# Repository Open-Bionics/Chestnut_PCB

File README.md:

# Chestnut_PCB
Electronics &amp; software files for the Chestnut/Chestnut+ PCB for the Brunel hand

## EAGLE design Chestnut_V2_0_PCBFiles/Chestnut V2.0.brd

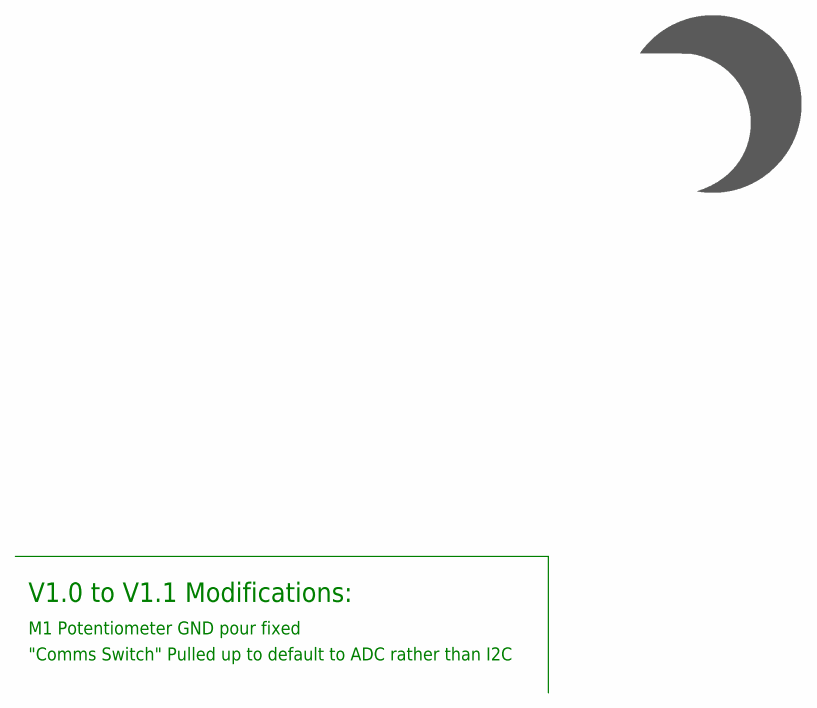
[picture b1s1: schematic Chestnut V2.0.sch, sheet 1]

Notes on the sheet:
V1.0 to V1.1 Modifications:
M1 Potentiometer GND pour fixed
"Comms Switch" Pulled up to default to ADC rather than I2C

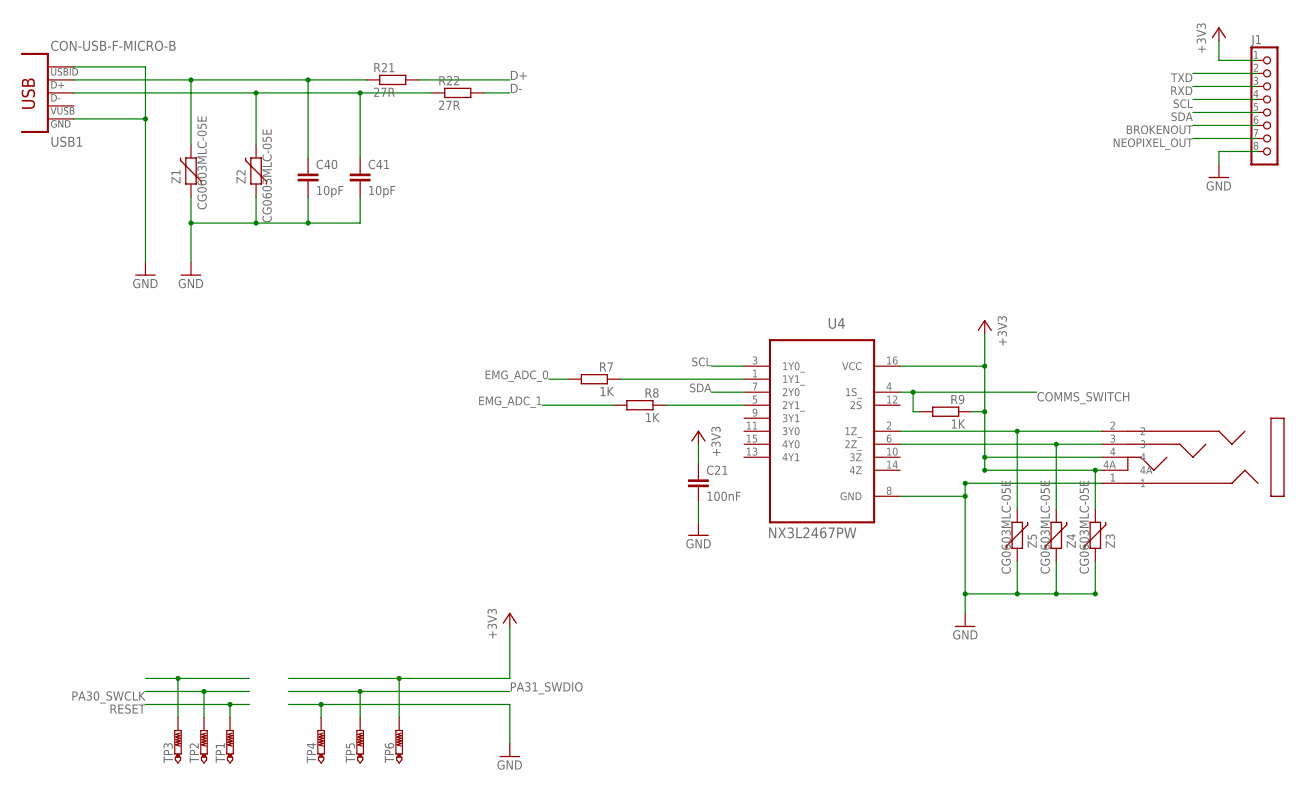
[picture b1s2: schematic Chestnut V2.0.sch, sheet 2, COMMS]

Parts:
C21: 100nF; C0402
C40, C41: 10pF; C0402
J1: CON_HEADER_1X08-PTH; M1X8
R7, R8, R9: 1K; R0402
R21, R22: 27R; R0402
TP1, TP2, TP3, TP4, TP5, TP6: PTR1TP11R; TP11R
U4: NX3L2467PW; SOP65P640X110-16N
U$7: LUMBERG_1503-13-VP3
USB1: CON-USB-F-MICRO-B; CONN_USB_MICRO-B
Z1, Z2, Z3, Z4, Z5: CG0603MLC-05E; CT/CN0603

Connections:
+3V3: C21.1, J1.1, R9.1, TP6.TP, U4.16 (VCC), U$7.4, U$7.4A, Z3.2; also elsewhere on the board
BROKENOUT: J1.6; also elsewhere on the board
COMMS_SWITCH: R9.2, U4.4 (1S_); also elsewhere on the board
D+: R21.2; also elsewhere on the board
D-: R22.2; also elsewhere on the board
EMG_ADC_0: R7.2; also elsewhere on the board
EMG_ADC_1: R8.2; also elsewhere on the board
GND: C21.2, C40.2, C41.2, J1.8, TP4.TP, U4.8 (GND), U$7.1, USB1.P4 (USBID), USB1.P5 (GND), Z1.1, Z2.1, Z3.1, Z4.1, Z5.1; also elsewhere on the board
unnamed: U4.6 (2Z_), U$7.3, Z4.2
unnamed: C41.1, R22.1, USB1.P2 (D-), Z2.2
unnamed: C40.1, R21.1, USB1.P3 (D+), Z1.2
unnamed: U4.2 (1Z_), U$7.2, Z5.2
unnamed: R7.1, U4.1 (1Y1_)
unnamed: R8.1, U4.5 (2Y1_)
NEOPIXEL_OUT: J1.7; also elsewhere on the board
PA30_SWCLK: TP2.TP; also elsewhere on the board
PA31_SWDIO: TP5.TP; also elsewhere on the board
RESET: TP1.TP; also elsewhere on the board
RXD: J1.3; also elsewhere on the board
SCL: J1.4, U4.3 (1Y0_); also elsewhere on the board
SDA: J1.5, U4.7 (2Y0); also elsewhere on the board
TXD: J1.2; also elsewhere on the board

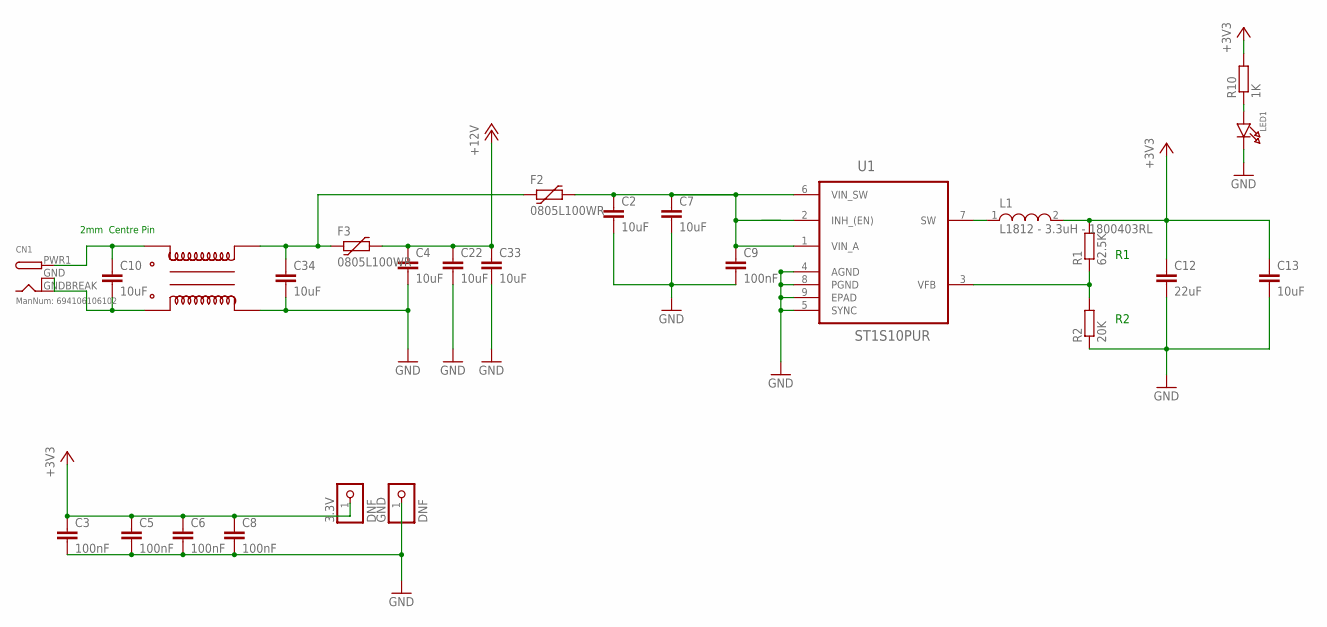
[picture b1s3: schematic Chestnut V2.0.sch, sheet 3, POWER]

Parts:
3.3V: DNF; 1X01_ROUND
C2, C4, C7, C10, C13, C22, C33, C34: 10uF; C0805
C3, C5, C6, C8, C9: 100nF; C0402
C12: 22uF; C1210
CN1: ManNum: 694106106102; DCJACK_2MM_SMT
F2, F3: 0805L100WR; PTC0805
GND: DNF; 1X01_ROUND
L1: L1812 - 3.3uH - 1800403RL; L1812
LED1: LED0603; CHIPLED_0603
R1: 62.5K; R0603
R2: 20K; R0603
R10: 1K; R0402
U1: ST1S10PUR; DFN400X400X100-9N
U$5: DLW5BTN501SQ2L

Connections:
12VFUSED: C2.1, C7.1, C9.1, F2.2, U1.1 (VIN_A), U1.2 (INH_(EN)), U1.6 (VIN_SW)
+3V3: 3.3V.1, C3.1, C5.1, C6.1, C8.1, C12.1, C13.1, L1.2, R1.2, R10.2; also elsewhere on the board
+12V: C4.1, C22.1, C33.1, F3.2; also elsewhere on the board
GND: C2.2, C3.2, C4.2, C5.2, C6.2, C7.2, C8.2, C9.2, C12.2, C13.2, C22.2, C33.2, C34.2, GND.1, LED1.C, R2.1, U1.4 (AGND), U1.5 (SYNC), U1.8 (PGND), U1.9 (EPAD), U$5.4; also elsewhere on the board
unnamed: LED1.A, R10.1
unnamed: L1.1, U1.7 (SW)
unnamed: C34.1, F2.1, F3.1, U$5.2
unnamed: R1.1, R2.2, U1.3 (VFB)
unnamed: C10.2, CN1.GND (GNDBREAK), CN1.GNDBREAK (GND), U$5.3
unnamed: C10.1, CN1.PWR1 (PWR), U$5.1

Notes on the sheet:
2mm Centre Pin

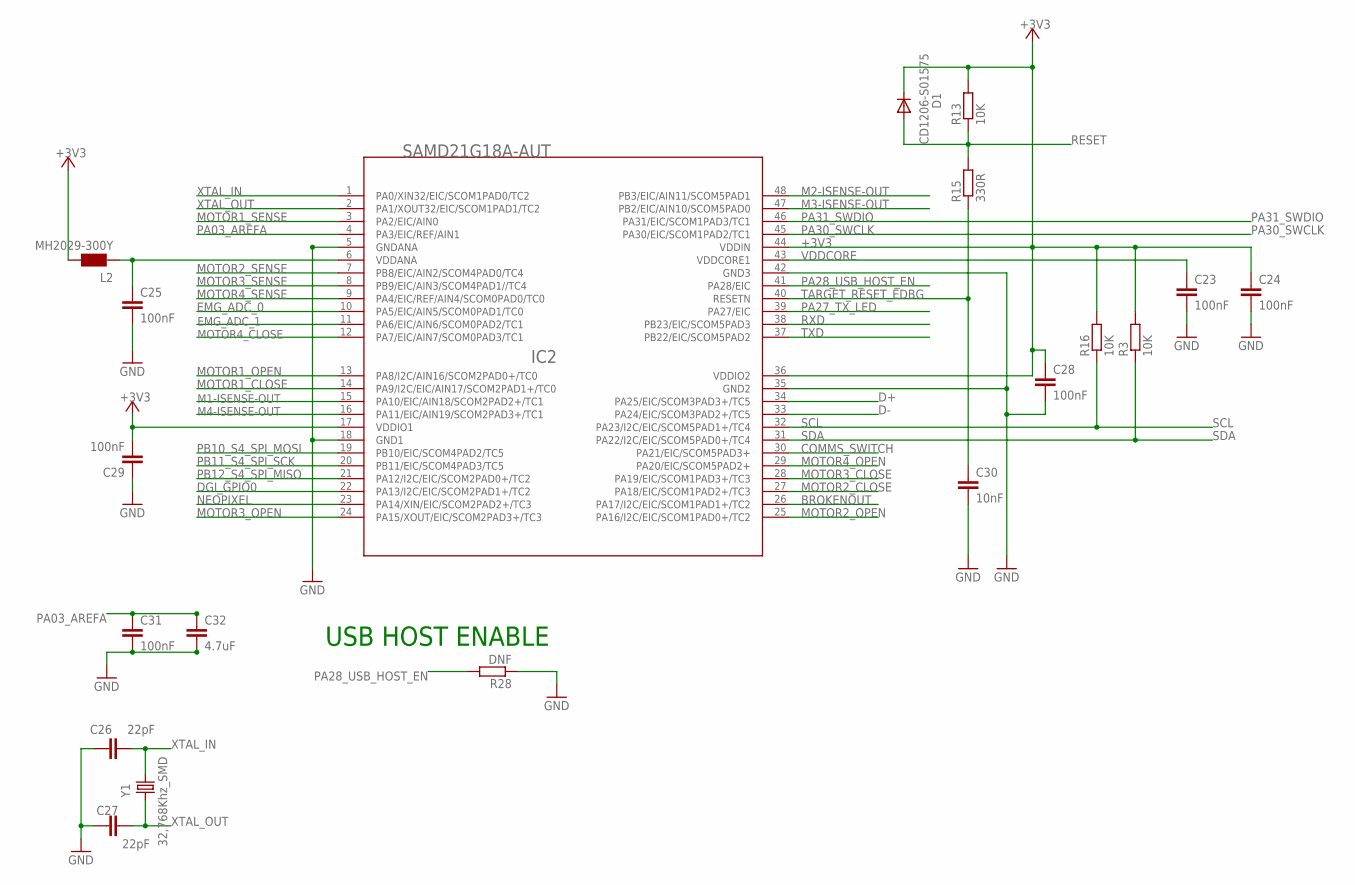
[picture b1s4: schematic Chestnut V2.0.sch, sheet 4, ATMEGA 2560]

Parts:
C23, C24, C25, C28, C29, C31: 100nF; C0402
C26, C27: 22pF; C0402
C30: 10nF; C0402
C32: 4.7uF; C0603
D1: CD1206-S01575; MINIMELF
IC2: SAMD21G18A-AUT; INTEGRATEDCIRCUITS_TQFP48-7X7
L2: MH2029-300Y; 0805
R3, R13, R16: 10K; R0402
R15: 330R; R0402
R28: DNF; R0402
Y1: 32,768Khz_SMD; RESONATOR_EPSON_FC_145

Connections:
+3V3: C24.1, C28.1, C29.2, D1.C, IC2.17 (VDDIO1), IC2.36 (VDDIO2), IC2.44 (VDDIN), L2.2, R3.2, R13.2, R16.2; also elsewhere on the board
BROKENOUT: IC2.26 (PA17/I2C/EIC/SCOM1PAD1+/TC2); also elsewhere on the board
COMMS_SWITCH: IC2.30 (PA21/EIC/SCOM5PAD3+); also elsewhere on the board
D+: IC2.34 (PA25/EIC/SCOM3PAD3+/TC5); also elsewhere on the board
D-: IC2.33 (PA24/EIC/SCOM3PAD2+/TC5); also elsewhere on the board
DGI_GPIO0: IC2.22 (PA13/I2C/EIC/SCOM2PAD1+/TC2)
EMG_ADC_0: IC2.10 (PA5/EIC/AIN5/SCOM0PAD1/TC0); also elsewhere on the board
EMG_ADC_1: IC2.11 (PA6/EIC/AIN6/SCOM0PAD2/TC1); also elsewhere on the board
GND: C23.2, C24.2, C25.2, C26.1, C27.1, C28.2, C29.1, C30.2, C31.2, C32.2, IC2.5 (GNDANA), IC2.18 (GND1), IC2.35 (GND2), IC2.42 (GND3), R28.1; also elsewhere on the board
M1-ISENSE-OUT: IC2.15 (PA10/EIC/AIN18/SCOM2PAD2+/TC1); also elsewhere on the board
M2-ISENSE-OUT: IC2.48 (PB3/EIC/AIN11/SCOM5PAD1); also elsewhere on the board
M3-ISENSE-OUT: IC2.47 (PB2/EIC/AIN10/SCOM5PAD0); also elsewhere on the board
M4-ISENSE-OUT: IC2.16 (PA11/EIC/AIN19/SCOM2PAD3+/TC1); also elsewhere on the board
MOTOR1_CLOSE: IC2.14 (PA9/I2C/EIC/AIN17/SCOM2PAD1+/TC0); also elsewhere on the board
MOTOR1_OPEN: IC2.13 (PA8/I2C/AIN16/SCOM2PAD0+/TC0); also elsewhere on the board
MOTOR1_SENSE: IC2.3 (PA2/EIC/AIN0); also elsewhere on the board
MOTOR2_CLOSE: IC2.27 (PA18/EIC/SCOM1PAD2+/TC3); also elsewhere on the board
MOTOR2_OPEN: IC2.25 (PA16/I2C/EIC/SCOM1PAD0+/TC2); also elsewhere on the board
MOTOR2_SENSE: IC2.7 (PB8/EIC/AIN2/SCOM4PAD0/TC4); also elsewhere on the board
MOTOR3_CLOSE: IC2.28 (PA19/EIC/SCOM1PAD3+/TC3); also elsewhere on the board
MOTOR3_OPEN: IC2.24 (PA15/XOUT/EIC/SCOM2PAD3+/TC3); also elsewhere on the board
MOTOR3_SENSE: IC2.8 (PB9/EIC/AIN3/SCOM4PAD1//TC4); also elsewhere on the board
MOTOR4_CLOSE: IC2.12 (PA7/EIC/AIN7/SCOM0PAD3/TC1); also elsewhere on the board
MOTOR4_OPEN: IC2.29 (PA20/EIC/SCOM5PAD2+); also elsewhere on the board
MOTOR4_SENSE: IC2.9 (PA4/EIC/REF/AIN4/SCOM0PAD0/TC0); also elsewhere on the board
unnamed: C25.1, IC2.6 (VDDANA), L2.1
NEOPIXEL: IC2.23 (PA14/XIN/EIC/SCOM2PAD2+/TC3); also elsewhere on the board
PA03_AREFA: C31.1, C32.1, IC2.4 (PA3/EIC/REF/AIN1)
PA27_TX_LED: IC2.39 (PA27/EIC)
PA28_USB_HOST_EN: IC2.41 (PA28/EIC), R28.2
PA30_SWCLK: IC2.45 (PA30/EIC/SCOM1PAD2/TC1); also elsewhere on the board
PA31_SWDIO: IC2.46 (PA31/EIC/SCOM1PAD3/TC1); also elsewhere on the board
PB10_S4_SPI_MOSI: IC2.19 (PB10/EIC/SCOM4PAD2/TC5)
PB11_S4_SPI_SCK: IC2.20 (PB11/EIC/SCOM4PAD3/TC5)
PB12_S4_SPI_MISO: IC2.21 (PA12/I2C/EIC/SCOM2PAD0+/TC2)
RESET: D1.A, R13.1, R15.2; also elsewhere on the board
RXD: IC2.38 (PB23/EIC/SCOM5PAD3); also elsewhere on the board
SCL: IC2.32 (PA23/I2C/EIC/SCOM5PAD1+/TC4), R16.1; also elsewhere on the board
SDA: IC2.31 (PA22/I2C/EIC/SCOM5PAD0+/TC4), R3.1; also elsewhere on the board
TARGET_RESET_EDBG: C30.1, IC2.40 (RESETN), R15.1
TXD: IC2.37 (PB22/EIC/SCOM5PAD2); also elsewhere on the board
VDDCORE: C23.1, IC2.43 (VDDCORE1)
XTAL_IN: C26.2, IC2.1 (PA0/XIN32/EIC/SCOM1PAD0/TC2), Y1.P$2 (2)
XTAL_OUT: C27.2, IC2.2 (PA1/XOUT32/EIC/SCOM1PAD1/TC2), Y1.P$1 (1)

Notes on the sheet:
USB HOST ENABLE

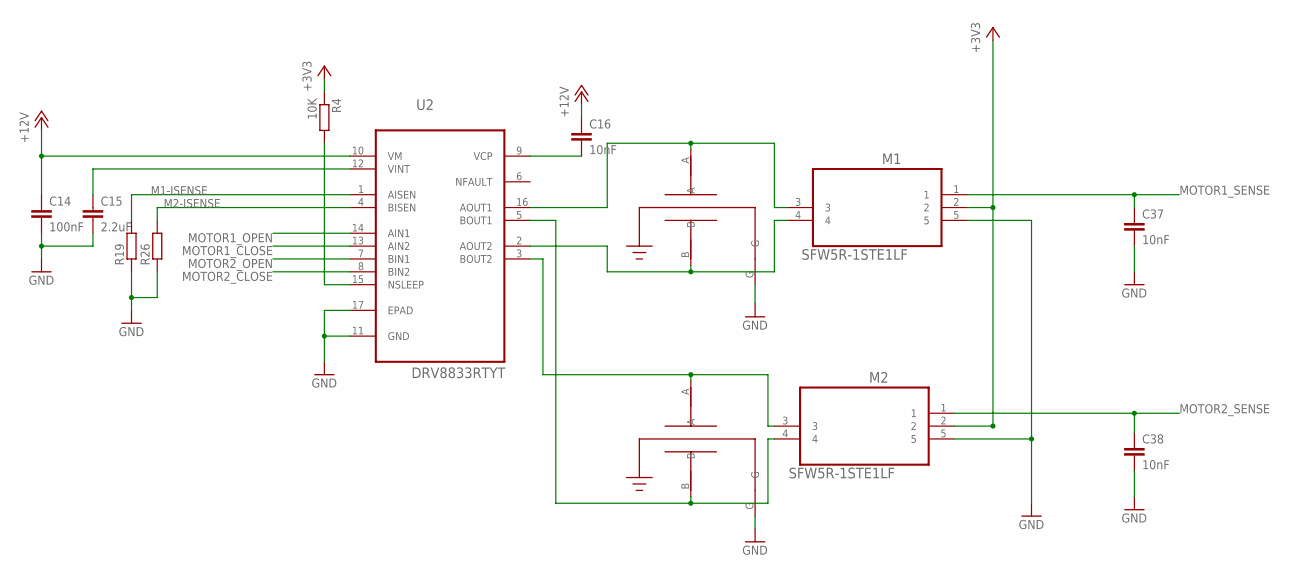
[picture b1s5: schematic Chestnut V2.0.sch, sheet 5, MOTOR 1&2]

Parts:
C14: 100nF; C0402
C15: 2.2uF; C0603
C16, C37, C38: 10nF; C0402
M1, M2: SFW5R-1STE1LF; FCI_SFW5R-1STE1LF
R4: 10K; R0402
R19, R26: R-EU_R0805; R0805
U2: DRV8833RTYT; QFN65P400X400X80-17N
U$8, U$19: 101X14N330MV4T_X2Y_0603

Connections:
+3V3: M1.2, M2.2, R4.1; also elsewhere on the board
+12V: C14.1, C16.1, U2.10 (VM); also elsewhere on the board
GND: C14.2, C15.2, C37.2, C38.2, M1.5, M2.5, R19.1, R26.1, U2.11 (GND), U2.17 (EPAD), U$8.G, U$19.G; also elsewhere on the board
M1-ISENSE: R19.2, U2.1 (AISEN); also elsewhere on the board
M2-ISENSE: R26.2, U2.4 (BISEN); also elsewhere on the board
MOTOR1_CLOSE: U2.13 (AIN2); also elsewhere on the board
MOTOR1_OPEN: U2.14 (AIN1); also elsewhere on the board
MOTOR1_SENSE: C37.1, M1.1; also elsewhere on the board
MOTOR2_CLOSE: U2.8 (BIN2); also elsewhere on the board
MOTOR2_OPEN: U2.7 (BIN1); also elsewhere on the board
MOTOR2_SENSE: C38.1, M2.1; also elsewhere on the board
unnamed: C16.2, U2.9 (VCP)
unnamed: M1.3, U2.16 (AOUT1), U$19.A
unnamed: M1.4, U2.2 (AOUT2), U$19.B
unnamed: M2.4, U2.5 (BOUT1), U$8.B
unnamed: M2.3, U2.3 (BOUT2), U$8.A
unnamed: R4.2, U2.15 (NSLEEP)
unnamed: C15.1, U2.12 (VINT)

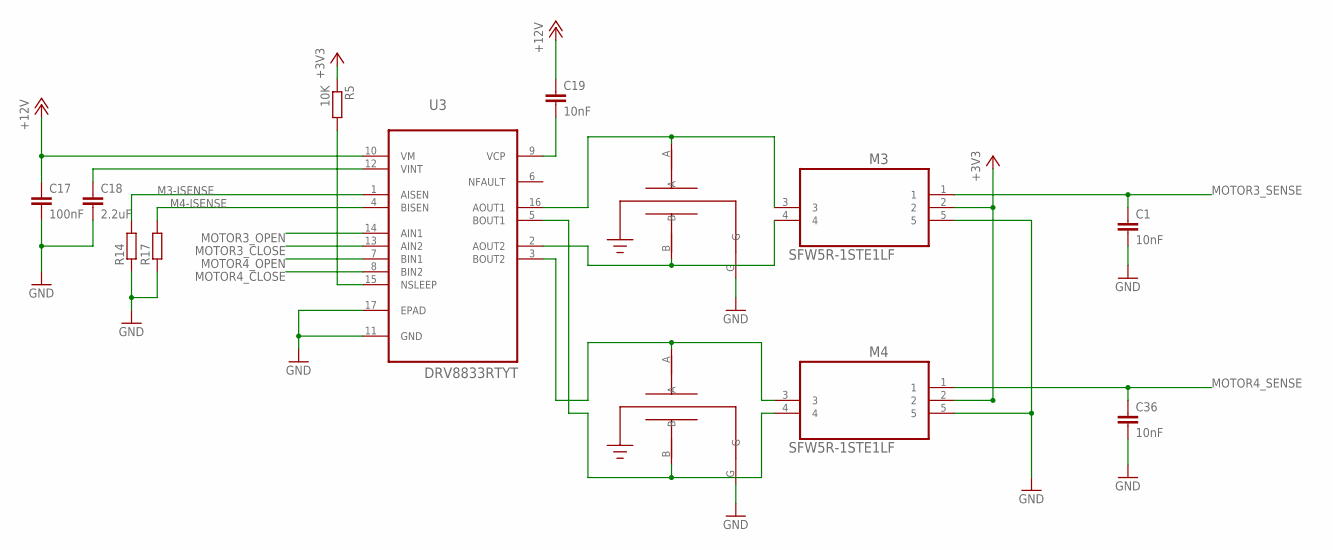
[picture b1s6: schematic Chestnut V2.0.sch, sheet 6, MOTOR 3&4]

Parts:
C1, C19, C36: 10nF; C0402
C17: 100nF; C0402
C18: 2.2uF; C0603
M3, M4: SFW5R-1STE1LF; FCI_SFW5R-1STE1LF
R5: 10K; R0402
R14, R17: R-EU_R0805; R0805
U3: DRV8833RTYT; QFN65P400X400X80-17N
U$9, U$10: 101X14N330MV4T_X2Y_0603

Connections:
+3V3: M3.2, M4.2, R5.1; also elsewhere on the board
+12V: C17.1, C19.1, U3.10 (VM); also elsewhere on the board
GND: C1.2, C17.2, C18.2, C36.2, M3.5, M4.5, R14.1, R17.1, U3.11 (GND), U3.17 (EPAD), U$9.G, U$10.G; also elsewhere on the board
M3-ISENSE: R14.2, U3.1 (AISEN); also elsewhere on the board
M4-ISENSE: R17.2, U3.4 (BISEN); also elsewhere on the board
MOTOR3_CLOSE: U3.13 (AIN2); also elsewhere on the board
MOTOR3_OPEN: U3.14 (AIN1); also elsewhere on the board
MOTOR3_SENSE: C1.1, M3.1; also elsewhere on the board
MOTOR4_CLOSE: U3.8 (BIN2); also elsewhere on the board
MOTOR4_OPEN: U3.7 (BIN1); also elsewhere on the board
MOTOR4_SENSE: C36.1, M4.1; also elsewhere on the board
unnamed: M3.3, U3.16 (AOUT1), U$9.A
unnamed: M3.4, U3.2 (AOUT2), U$9.B
unnamed: M4.4, U3.5 (BOUT1), U$10.B
unnamed: M4.3, U3.3 (BOUT2), U$10.A
unnamed: C19.2, U3.9 (VCP)
unnamed: C18.1, U3.12 (VINT)
unnamed: R5.2, U3.15 (NSLEEP)

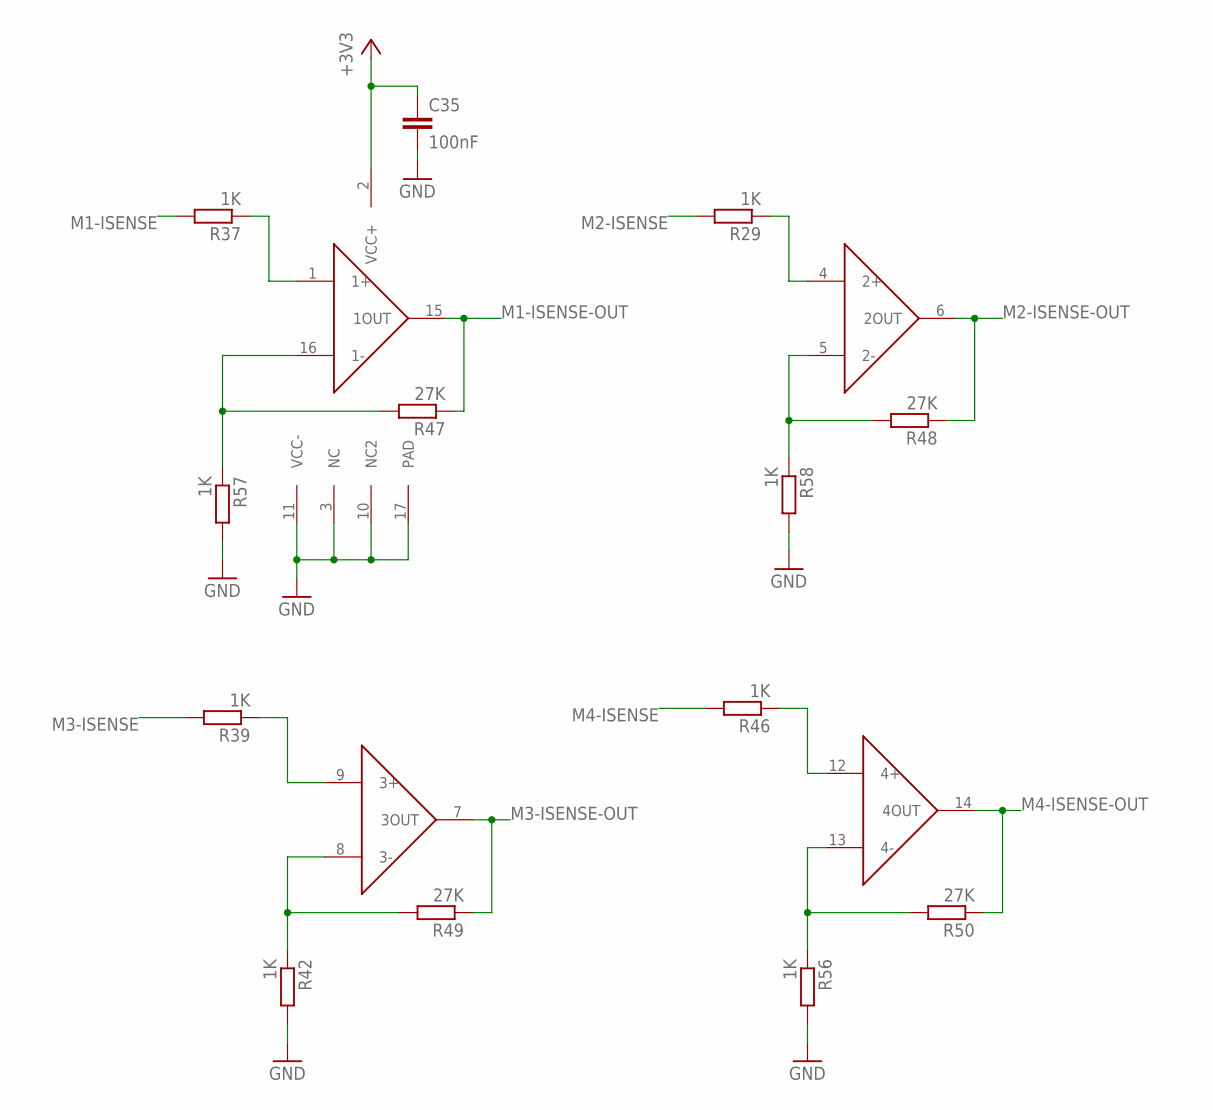
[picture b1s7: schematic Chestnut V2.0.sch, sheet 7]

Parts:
C35: 100nF; C0402
R29, R37, R39, R42, R46, R56, R57, R58: 1K; R0402
R47, R48, R49, R50: 27K; R0402
U$15: TSZ124IQ4T

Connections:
+3V3: C35.1, U$15.2 (VCC+); also elsewhere on the board
GND: C35.2, R42.2, R56.2, R57.2, R58.2, U$15.3 (NC), U$15.10 (NC2), U$15.11 (VCC-), U$15.17 (PAD); also elsewhere on the board
M1-ISENSE: R37.2; also elsewhere on the board
M1-ISENSE-OUT: R47.1, U$15.15 (1OUT); also elsewhere on the board
M2-ISENSE: R29.2; also elsewhere on the board
M2-ISENSE-OUT: R48.1, U$15.6 (2OUT); also elsewhere on the board
M3-ISENSE: R39.2; also elsewhere on the board
M3-ISENSE-OUT: R49.1, U$15.7 (3OUT); also elsewhere on the board
M4-ISENSE: R46.2; also elsewhere on the board
M4-ISENSE-OUT: R50.1, U$15.14 (4OUT); also elsewhere on the board
unnamed: R37.1, U$15.1 (1+)
unnamed: R29.1, U$15.4 (2+)
unnamed: R39.1, U$15.9 (3+)
unnamed: R47.2, R57.1, U$15.16 (1-)
unnamed: R46.1, U$15.12 (4+)
unnamed: R48.2, R58.1, U$15.5 (2-)
unnamed: R42.1, R49.2, U$15.8 (3-)
unnamed: R50.2, R56.1, U$15.13 (4-)

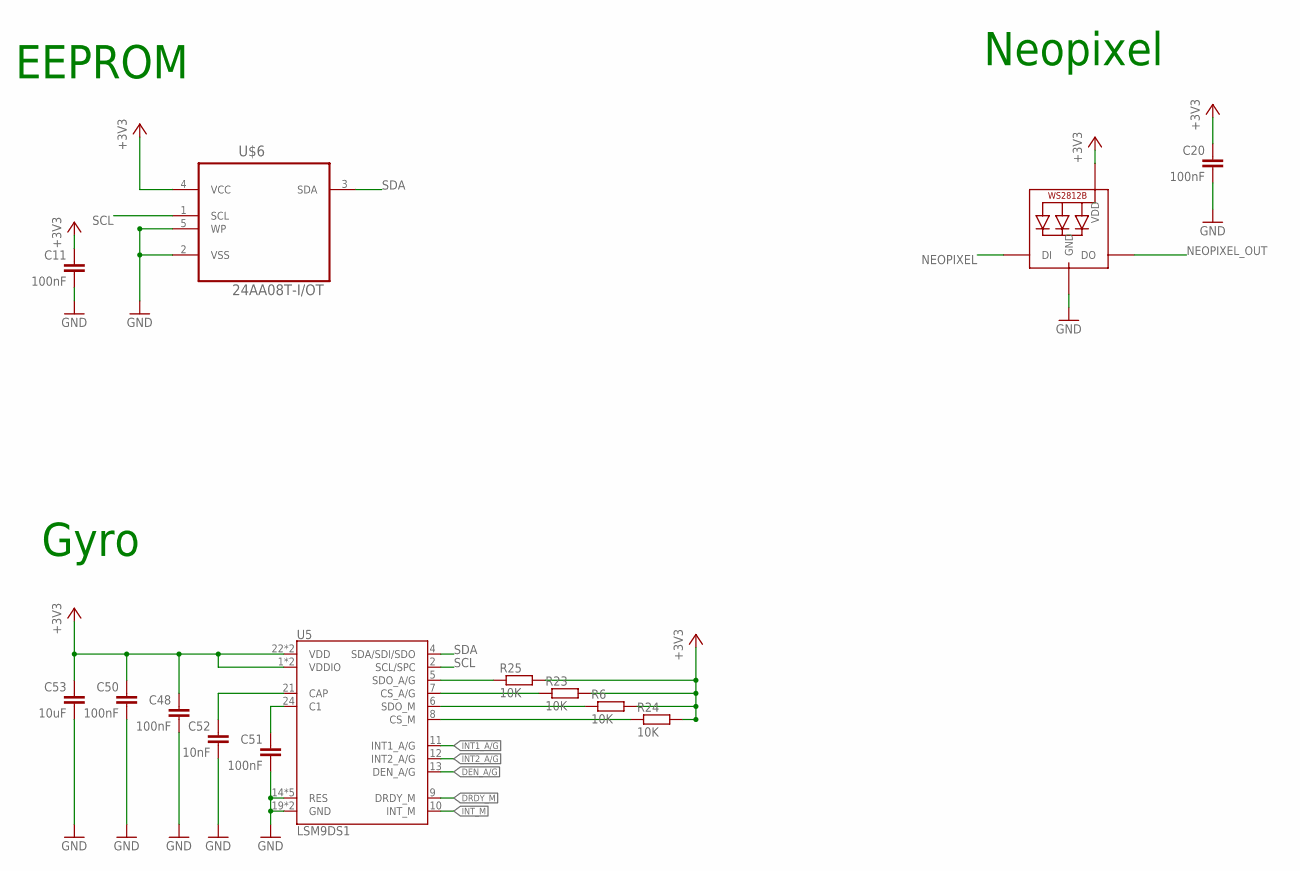
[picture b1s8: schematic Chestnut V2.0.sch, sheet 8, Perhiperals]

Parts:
C11, C20, C48, C50, C51: 100nF; C0402
C52: 10nF; C0402
C53: 10uF; C0805
LED2: WS2812B3535; LED3535
R6, R23, R24, R25: 10K; R0402
U5: LSM9DS1; LGA24-8X4
U$6: 24AA08T-I/OT; SOT95P290X145-5N

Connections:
+3V3: C11.1, C20.1, C48.1, C50.1, C53.1, LED2.2 (VDD), R6.2, R23.2, R24.2, R25.2, U5.1 (VDDIO), U5.3 (VDDIO), U5.22 (VDD), U5.23 (VDD), U$6.4 (VCC); also elsewhere on the board
C1: C51.1, U5.24 (C1)
CAP: C52.1, U5.21 (CAP)
DEN_A/G: U5.13 (DEN_A/G)
DRDY_M: U5.9 (DRDY_M)
GND: C11.2, C20.2, C48.2, C50.2, C51.2, C52.2, C53.2, LED2.4 (GND), U5.14 (RES), U5.15 (RES), U5.16 (RES), U5.17 (RES), U5.18 (RES), U5.19 (GND), U5.20 (GND), U$6.2 (VSS), U$6.5 (WP); also elsewhere on the board
INT1_A/G: U5.11 (INT1_A/G)
INT2_A/G: U5.12 (INT2_A/G)
INT_M: U5.10 (INT_M)
unnamed: R25.1, U5.5 (SDO_A/G)
unnamed: R23.1, U5.7 (CS_A/G)
unnamed: R6.1, U5.6 (SDO_M)
unnamed: R24.1, U5.8 (CS_M)
NEOPIXEL: LED2.1 (DI); also elsewhere on the board
NEOPIXEL_OUT: LED2.3 (DO); also elsewhere on the board
SCL: U5.2 (SCL/SPC), U$6.1 (SCL); also elsewhere on the board
SDA: U5.4 (SDA/SDI/SDO), U$6.3 (SDA); also elsewhere on the board

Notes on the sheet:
EEPROM
Gyro
Neopixel

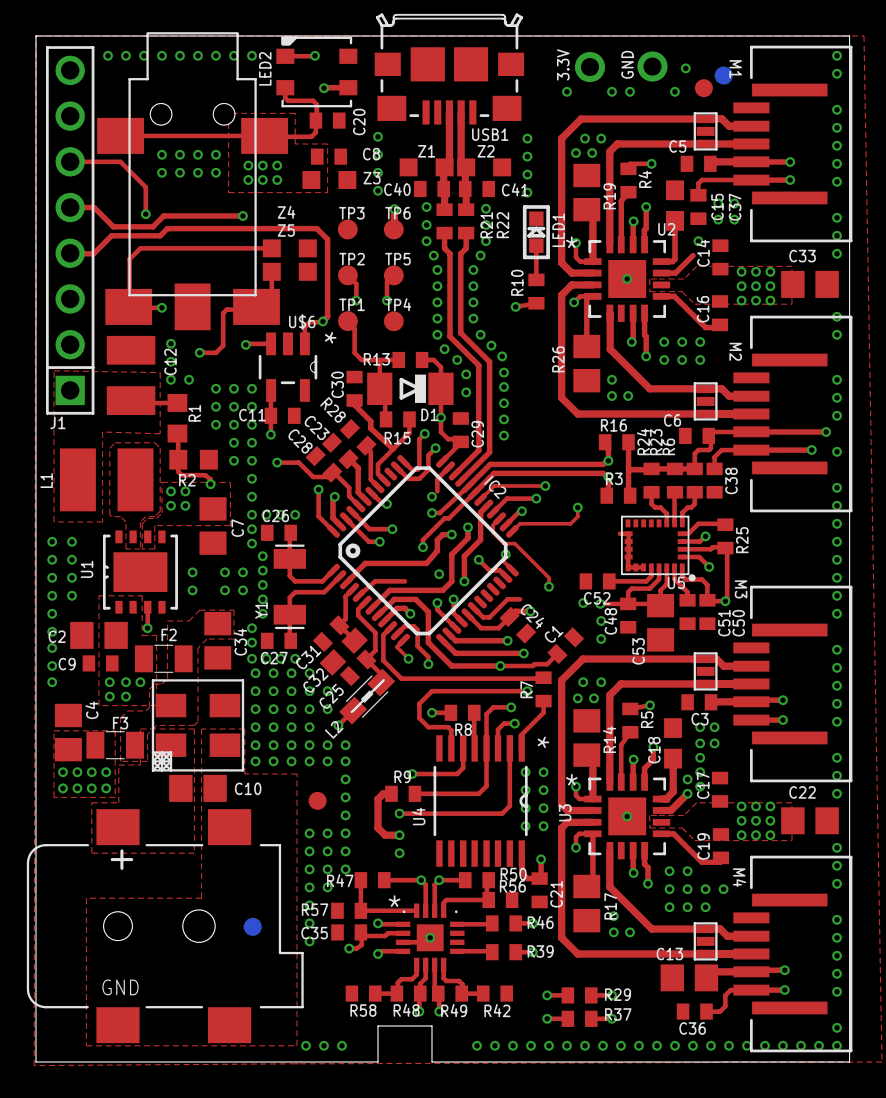
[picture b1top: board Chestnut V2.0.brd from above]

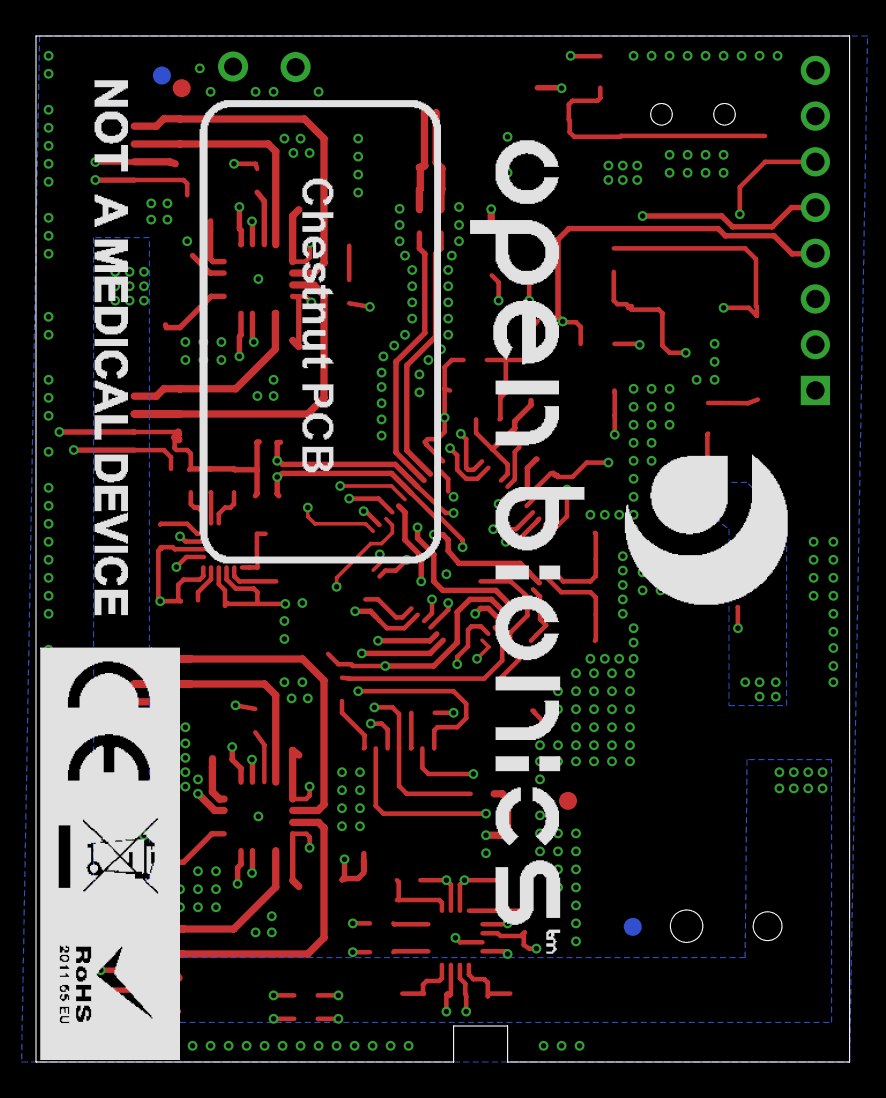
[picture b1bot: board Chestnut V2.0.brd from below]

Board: 4 copper layers, 45.2 x 57.0 mm, 126 parts (2 on the bottom side), 86 nets.

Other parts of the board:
U$1, U$2, U$3, U$4: FIDUCIAL_G10

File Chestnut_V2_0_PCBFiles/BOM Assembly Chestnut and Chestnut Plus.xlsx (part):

Qty | Value | Device | Package | Parts | Description | Chestnut Fit | Chestnut Plus Fit | Manufacturer Part No. | Supplier | Link | Cost / 100 | Cost Per Unit Chestnut | Cost Per Unit Chestnut +
2 | DNF | HEADER-1X1ROUND | 1X01_ROUND | 3.3V, GND | PIN HEADER | N | N | N/A | N/A | N/A | 0 | 0 | 0
8 | 10nF | C-EUC0402 | C0402 | C1, C16, C19, C30, C36, C37, C38, C52 | CAPACITOR, European symbol | Y | Y | GRM155R71E103KA01D | Mouser | http://www.mouser.co.uk/ProductDetail/Murata/GRM155R71E103KA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 | 3.0000000000000001E-3 | 2.4E-2 | 2.4E-2
1 | 22uF | C-EUC1210 | C1210 | C12 | CAPACITOR, European symbol | Y | Y | GRM32ER61E226KE15L | Mouser | http://www.mouser.co.uk/ProductDetail/Murata/GRM32ER61E226KE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 | 0.183 | 0.183 | 0.183
2 | 2.2uF | C-EUC0603 | C0603 | C15, C18 | CAPACITOR, European symbol | Y | Y | GRM188R71A225KE15D | Mouser | http://www.mouser.co.uk/ProductDetail/Murata/GRM188R71A225KE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 | 8.6999999999999994E-2 | 0.17399999999999999 | 0.17399999999999999
9 | 10uF | C-EUC0805 | C0805 | C2, C4, C7, C10, C13, C22, C33, C34, C53 | CAPACITOR, European symbol | Y | Y | GRM21BR61E106KA73L | Mouser | http://www.mouser.co.uk/ProductDetail/Murata/GRM21BR61E106KA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 | 3.6999999999999998E-2 | 0.33299999999999996 | 0.33299999999999996
2 | 22pF | C-EUC0402 | C0402 | C26, C27 | CAPACITOR, European symbol | Y | Y | 04025A220JAT2A | Mouser | http://www.mouser.co.uk/ProductDetail/AVX/04025A220JAT2A/?qs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 | 2.4E-2 | 4.8000000000000001E-2 | 4.8000000000000001E-2
20 | 100nF | C-EUC0402 | C0402 | C3, C5, C6, C8, C9, C11, C14, C17, C20, C21, C23, C24, C25, C28, C29, C31, C35,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 | CAPACITOR, European symbol | Y | Y | CGA2B3X7R1H104K050BB | Mouser | http://www.mouser.co.uk/ProductDetail/TDK/CGA2B3X7R1H104K050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 | 3.2000000000000001E-2 | 0.64 | 0.64
1 | 4.7uF | C-EUC0603 | C0603 | C32 | CAPACITOR, European symbol | Y | Y | GRM188R6YA475KE15D | Mouser | http://www.mouser.co.uk/ProductDetail/Murata/GRM188R6YA475KE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 | 7.0999999999999994E-2 | 7.0999999999999994E-2 | 7.0999999999999994E-2
2 | 10pF | C-EUC0402 | C0402 | C40, C41 | CAPACITOR, European symbol | Y | Y | GRM1555C1H100JA01D | Mouser | http://www.mouser.co.uk/ProductDetail/Murata/GRM1555C1H100JA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 | 3.0000000000000001E-3 | 6.0000000000000001E-3 | 6.0000000000000001E-3
1 | ManNum: 694106106102 | DCBARRELSMT | DCJACK_2MM_SMT | CN1 | 2.0mm DC Barrel Jack | Y | Y | Wurth 694106106102 | Mouser | http://www.mouser.co.uk/ProductDetail/Wurth-Electronics/6941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 | 0.92200000000000004 | 0.92200000000000004 | 0.92200000000000004
1 | CD1206-S01575 | 0012_CD1206-S01575 | MINIMELF | D1 | small-signal high-speed Switching Diodes CD1206 | Y | Y | CD1206-S01575 | Mouser | http://www.mouser.co.uk/ProductDetail/Bourns/CD1206-S01575/?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 | 0.04 | 0.04 | 0.04
1 | 0805L100WR | FUSE_PTC-0805 | PTC0805 | F2 | Resettable PTC | Y | Y | 0805L100WR | Farnell | http://uk.farnell.com/littelfuse/0805l100wr/resettable-fuse-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 | 0.86 | 0.86 | 0.86
1 | MCF0805B2R00FSTR | FUSE_PTC-0805 | PTC0805 | F3 | Resettable PTC | Y | Y | MCF0805B2R00FSTR | Farnell | http://uk.farnell.com/multicomp/mcf0805b2r00fstr/fuse-smd-08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 | 0.40699999999999997 | 0.40699999999999997 | 0.40699999999999997
1 | SAMD21G18A-AUT | INTEGRATEDCIRCUITS_1792_SAMD21G18A-AUT | INTEGRATEDCIRCUITS_TQFP48-7X7 | IC2 | Atmel D21 32bit ARM Cortex-M0 microcontroller - 48 PIN | Y | Y | ATSAMD21G18A-AUT | Mouser | http://www.mouser.co.uk/ProductDetail/Atmel/ATSAMD21G18A-AUT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 | 2.88 | 2.88 | 2.88
1 | CON_HEADER_1X08-PTH | CON_HEADER_1X08-PTH | M1X8 | J1 |  | N | N | N/A | N/A | N/A | 0 | 0 | 0
1 | L1812 - 3.3uH - 1800403RL | INDUCTOR-L1812 | L1812 | L1 | Inductor | Y | Y | 744045003 | Mouser | http://www.mouser.co.uk/ProductDetail/Wurth-Electronics/7440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 | 0.47099999999999997 | 0.47099999999999997 | 0.47099999999999997
1 | MH2029-300Y | 0001_BLM21PG300SN1D_/_MH2029-300Y | 805 | L2 | BLM21 | Y | Y | MH2029-300Y | Mouser | http://www.mouser.co.uk/ProductDetail/Bourns/MH2029-300Y/?qs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 | 2.8000000000000001E-2 | 2.8000000000000001E-2 | 2.8000000000000001E-2
1 |  | LED0603 | CHIPLED_0603 | LED1 | LED | Y | Y | LG Q396-PS-35 | Mouser | http://www.mouser.co.uk/ProductDetail/OSRAM-Opto-Semiconduct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 | 7.5999999999999998E-2 | 7.5999999999999998E-2 | 7.5999999999999998E-2
1 | WS2812B3535 | WS2812B3535 | LED3535 | LED2 |  | Y | Y | WS2812B3535 | DigiKey | https://www.digikey.co.uk/product-detail/en/adafruit-industr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 | 0.33 | 0.33 | 0.33
4 | SFW5R-1STE1LF | SFW5R-1STE1LF | FCI_SFW5R-1STE1LF | M1, M2, M3, M4 | FFC/FPC CONNECTOR, RECEPTACLE, 5POS 1ROW | Y | Y | SFW5R-1STE1LF | Mouser | http://www.mouser.co.uk/ProductDetail/FCI-Amphenol/SFW5R-1ST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 | 0.36799999999999999 | 1.472 | 1.472
1 | 62.5K | R-EU_R0603 | R0603 | R1 | RESISTOR, European symbol | Y | Y | CRCW0603100KFKEA | Mouser | http://www.mouser.co.uk/ProductDetail/Vishay-Dale/CRCW060310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 | 1.9E-2 | 1.9E-2 | 1.9E-2
4 | 0.47R | R-EU_R0805 | R0805 | R14, R17, R19, R26 | RESISTOR, European symbol | Y | Y | RL0805FR-7W0R47L | Mouser | http://www.mouser.co.uk/ProductDetail/Yageo/RL0805FR-7W0R47L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 | 6.2E-2 | 0.248 | 0.248
1 | 330R | R-EU_R0402 | R0402 | R15 | RESISTOR, European symbol | Y | Y | RC0402FR-07330RL | Mouser | http://www.mouser.co.uk/ProductDetail/Yageo/RC0402FR-07330RL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 | 2E-3 | 2E-3 | 2E-3
1 | 20K | R-EU_R0603 | R0603 | R2 | RESISTOR, European symbol | Y | Y | CRCW060319K1FKEA | Mouser | http://www.mouser.co.uk/ProductDetail/Vishay/CRCW060319K1FKE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 | 1.9E-2 | 1.9E-2 | 1.9E-2
2 | 27R | R-EU_R0402 | R0402 | R21, R22 | RESISTOR, European symbol | Y | Y | RC0402JR-0727RL | Mouser | http://www.mouser.co.uk/ProductDetail/Yageo/RC0402JR-0727RL/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 | 2E-3 | 4.0000000000000001E-3 | 4.0000000000000001E-3
1 | DNF | R-EU_R0402 | R0402 | R28 | RESISTOR, European symbol | N | N | N/A | N/A | N/A | 0 | 0 | 0
9 | 10K | R-EU_R0402 | R0402 | R3, R4, R5, R6, R13, R16, R23, R24, R25 | RESISTOR, European symbol | Y | Y | CRCW040210K0FKED | Mouser | http://www.mouser.co.uk/ProductDetail/Vishay-Dale/CRCW040210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 | 1.9E-2 | 0.17099999999999999 | 0.17099999999999999
4 | 27K | R-EU_R0402 | R0402 | R47, R48, R49, R50 | RESISTOR, European symbol | Y | Y | CRCW040227K0FKED | Mouser | http://www.mouser.co.uk/ProductDetail/Vishay-Dale/CRCW040227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 | 1.9E-2 | 7.5999999999999998E-2 | 7.5999999999999998E-2
12 | 1K | R-EU_R0402 | R0402 | R7, R8, R9, R29, R37, R39, R42, R46, R56, R57, R58, R10 | RESISTOR, European symbol | Y | Y | RC0402JR-071KL | Mouser | http://www.mouser.co.uk/ProductDetail/Yageo/RC0402JR-071KL/?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 | 2E-3 | 2.4E-2 | 2.4E-2
6 | PTR1TP11R | PTR1TP11R | TP11R | TP1, TP2, TP3, TP4, TP5, TP6 | TEST PIN | N | N | N/A | N/A | N/A | 0 | 0 | 0
1 | TSZ124IQ4T | TSZ124IQ4T | TSZ124IQ4T | U$15 |  | N | Y | TSZ124IQ4T | Mouser | http://www.mouser.co.uk/ProductDetail/STMicroelectronics/TSZ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 | 1.4 | 0 | 1.4
1 | DLW5BTN501SQ2L | DLW5BTN501SQ2L | DLW5BTN501SQ2L | U$5 |  | Y | Y | DLW5BTN501SQ2L | Mouser | http://www.mouser.co.uk/ProductDetail/Murata/DLW5BTN501SQ2L/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 | 0.53900000000000003 | 0.53900000000000003 | 0.53900000000000003
1 | 24AA08T-I/OT | 24AA08T-I/OT | SOT95P290X145-5N | U$6 | 8K I2C Serial EEPROM | Y | Y | 24AA08T-I/OT | Mouser | http://www.mouser.co.uk/ProductDetail/Microchip/24AA08T-I-OT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 | 0.17499999999999999 | 0.17499999999999999 | 0.17499999999999999
1 | LUMBERG_1503-13-VP3 | LUMBERG_1503-13-VP3 | LUMBERG_1503-13-VP3 | U$7 |  | Y | Y | 1503 13 VP3 | Farnell | http://uk.farnell.com/lumberg/1503-13-vp3/socket-3-5mm-jack-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 | 0.71399999999999997 | 0.71399999999999997 | 0.71399999999999997
4 | 101X14N330MV4T_X2Y_0603 | 101X14N330MV4T_X2Y_0603 | 101X14N330MV4T_X2Y_0603 | U$8, U$9, U$10, U$19 |  | Y | Y | 500X14W103MV4T | Mouser | http://www.mouser.co.uk/ProductDetail/Johanson/500X14W103MV4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 | 9.0999999999999998E-2 | 0.36399999999999999 | 0.36399999999999999
1 | ST1S10PUR | ST1S10PUR | DFN400X400X100-9N | U1 | BUCK, 2.5-18V, 900KHZ, 3A, 0.8V, 8DFN | Y | Y | ST1S10PUR | Mouser | http://www.mouser.co.uk/ProductDetail/STMicroelectronics/ST1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 | 0.93 | 0.93 | 0.93
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
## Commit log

2017-01-09 Added Arduino board manager file
2017-01-09 Added openbionics-samd-1.0.0.tar
2017-01-10 Added PIN_A9
2017-01-12 Removed Chestnut+
2017-01-24 Updated core README
2017-08-08 Added brd files
2017-08-15 Added Chestnut Datasheet

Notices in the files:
parts and their libraries:
microbuilder: This work is placed in the public domain, and may be freely used for commercial and non-commercial work with the following conditions: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
dicons: Copyright (C) 2004, Bob Starr (rtzaudio@mindspring.com)
